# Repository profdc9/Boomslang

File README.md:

# Boomslang

A 3-channel ESP32-S3 pyrotechnic/model-rocket ignition controller. Hardware
(KiCad project, schematic, gerbers) is under `Boomslang/`; firmware is under
`firmware/` (PlatformIO, Arduino framework).

## ⚠️ Disclaimer — use at your own risk

This project fires pyrotechnic devices and/or model rocket motors. Incorrect
wiring, misconfiguration, a firmware bug, a hardware fault, or plain
operator error can cause unintended ignition, fire, injury, or property
damage. **This is a hobbyist project, provided AS-IS, with NO WARRANTY OF
ANY KIND** — express or implied, including no warranty of merchantability,
fitness for a particular purpose, or that it is safe, correct, reliable, or
free of defects.

By building, modifying, or using this hardware or firmware, you accept full
responsibility for:

- Verifying correct operation yourself, on your own hardware, before relying
  on any of it — including every safety feature described in this README.
- Complying with all applicable laws, regulations, and permitting
  requirements for pyrotechnics, explosives, and/or model rocketry in your
  jurisdiction.
- Following standard range-safety practice: safe distances, no bystanders
  in range, appropriate PPE, a real mechanical arm switch you trust, and
  never treating any software feature here as a substitute for that.

The author(s) and contributors accept **no liability** for any injury,
death, damage, or loss arising from building, modifying, or using this
project, to the fullest extent permitted by law.

## License

Dual-licensed by design, since this repo mixes source code and hardware
design files:

- **Firmware** (`firmware/`) is licensed under the [MIT License](LICENSE).
- **Hardware design files** (`Boomslang/` — KiCad schematic, PCB, gerbers)
  are licensed under [CC BY-SA 4.0](LICENSE-HARDWARE.txt).

Both are permissive and allow commercial use, but neither one waives the
disclaimer above — "you can use/modify/redistribute this" is a separate
question from "this is safe or fit for any particular purpose."

## WiFi access

The board hosts its own WiFi AP (no router needed) — SSID and password are
persisted settings (`wifiSsid`/`wifiPassword`, settings page), defaulting to
`boomslang` / `liftoff!`. **The password is this device's only access
control** — there's no separate login on top of it, so anyone who has it can
arm and fire. Change it from the default before using this anywhere it
matters. A password can also be left blank for an open, unencrypted network,
but that isn't recommended for the same reason.

Changes take effect only after the device is power-cycled or reset (the AP
isn't re-initialized at runtime) — you'll need to reconnect using the new
name/password afterward. SSID must be 1-32 characters; password must be
empty or 8-63 characters (the minimum WPA2-PSK allows).

The control pages are served over plain HTTP, not HTTPS — WPA2 already
encrypts the WiFi link itself, and adding TLS on top would mean a
self-signed certificate that a phone would flag as untrusted on every visit,
plus added latency on the page's frequent status polling, for a narrower
additional threat (another authenticated client on the same AP sniffing
traffic) than what WPA2 already covers.

**Relay (station) mode** (`wifiStationMode`, default **off**): instead of
hosting its own AP, the device can join `wifiSsid`/`wifiPassword` as a
client of an existing router, to relay through it when the operator needs
more distance from the pyrotechnics than the device's own AP range allows.
If it can't connect within 15 seconds (wrong password, out of range, router
down), it falls back to hosting its own AP instead — so a bad relay network
never leaves you locked out of the device with no way to disarm or abort.

This setting is deliberately **not a checkbox** on the settings page:
enabling it means anyone who can reach that external network can also reach
this device, so it requires typing the literal word `relay` into a text
box rather than a single accidental tap — blank or anything else both mean
"stay off, host my own AP" (the safe default), including if the field is
missing from the request entirely.

**Before you enable this, secure that router/network yourself — it's now
part of your access control, not just Boomslang's own password.** In its
own AP mode, WPA2 on the device is the entire perimeter. In relay mode,
that perimeter is whatever the router enforces: WPA2/WPA3 with a strong
password of its own, no other untrusted devices or guests on it, and
ideally a network used for nothing but this. A relay network that's open,
weakly secured, or shared with devices you don't control gives *anyone on
it* the same access as someone standing next to the device with its own
password — arming and firing included.

Either way — hosting an AP or joined as a station — the device also starts
an mDNS responder, so `http://boomslang.local` works regardless of which
mode ended up active or what IP a router's DHCP server happened to assign.

## Web UI pages

Four pages, all polling `/status.json` and posting to the same handful of
endpoints — the split below is purely how the browser organizes things, not
a backend/data-model split. Each has a small nav row (Main · Timing · Stats
· Settings) so it's obvious how to get back to the others.

- **`/` (Main)** — the operational screen, meant for actual field use:
  arm/fault/lockout status, battery voltage, each channel's checkbox + live
  continuity/firing state, and TRIGGER/ABORT/PANIC. Deliberately lean —
  timing setup and post-fire review live elsewhere so this screen stays fast
  to read and tap through during an actual arm/fire sequence.
- **`/timing`** — setup screen: the same channel checkboxes as Main (same
  `/select` endpoint — selection can be changed from either page) plus each
  channel's offset/duration in milliseconds and optional PWM cycling
  (Hz/duty%, see Trigger sequence below). No live operational state and no
  TRIGGER/ABORT/PANIC here.
- **`/stats`** — read-only review: peak and average current per channel
  from its most recent pulse (see Trigger sequence below).
- **`/config` (Settings)** — every persisted setting described throughout
  this README.

## Overcurrent fault protection

Each channel's IRLZ44N MOSFET has its own analog overcurrent comparator
(transistors Q5/Q10/Q16, sensing the 0.05Ω source shunt) that pulls that
channel's own gate to GND in hardware, in nanoseconds, with **no firmware
involved at all**. That's the actual protection for the transistor. All
three channels' comparators also pull a single shared, open-collector,
active-LOW `FAULT` line (GPIO1) — since it's wired-OR across all three,
firmware can tell *that* a channel faulted, but not *which* one.

The 0.05Ω figure above is just the schematic default (R1/R17/R31) — the
per-channel shunt resistance (`senseOhms`, settings page) is a runtime
setting used for the firing-current math (`readCurrentA()`), independently
of the comparator's own fixed hardware trip point. Valid range is
**0.01Ω–100Ω**, to accommodate a field-replaced shunt of a different value.

**The fault ISR** (`onFaultISR` in `firmware/src/main.cpp`) is a level-1
`attachInterrupt` on `FAULT`, `IRAM_ATTR`, and deliberately minimal: it does
exactly two things, a single register write forcing all three TRIGGER
outputs HIGH at once (not just the channel that faulted — the shared line
can't tell which one anyway, so every channel is shut down for consistency)
and setting a sticky `faultLatched` flag. Nothing else runs in the ISR
itself — no `Serial`, no heap, and critically no `analogRead()`, since the
ESP-IDF ADC driver takes a FreeRTOS mutex internally that `loop()` is
already holding on a regular basis; taking it again from ISR context would
be undefined behavior.

**Sampling SENSE for diagnostics** (which channel was drawing how much
current right as the fault hit) therefore happens in a separate,
dedicated FreeRTOS task (`faultSampleTask`), woken by the ISR via
`vTaskNotifyGiveFromISR`/`portYIELD_FROM_ISR` so it runs essentially the
instant the ISR returns, ahead of `loop()` or anything else. It's pinned to
the core opposite the Arduino loop/web server, at a priority high enough to
preempt normal code but below WiFi's own internal tasks. This snapshot is
best-effort — the hardware protection may have already cut current before
it runs — and is exposed as `fault_snapshot_a` in `/status.json` and shown
in the FAULT banner on the control page. If the banner reads "FAULT —
overcurrent detected" with no `(X.XXA Y.YYA Z.ZZA)` after it, that means
`fault_snapshot_a` was never populated for this event — either
`writeTriggerPinBlanked()`'s own fallback latched the fault directly
(covered below; it takes its own snapshot too, since it's normal task
context rather than ISR context and can safely call `analogRead()`
itself, unlike `onFaultISR()`), or a fault was latched some other way that
doesn't notify `faultSampleTask` (the boot-time check, for example).

**Clearing a fault**: `faultLatched` is a software latch, not
self-clearing. It clears automatically — no button, no endpoint — the
instant the device is `DISARMED` and the hardware `FAULT` line re-checks
clear (several reads over ~2ms, so a line chattering right at the trip
point doesn't get cleared into a still-live fault; see `loop()`'s
DISARMED-only fault-clearing pass in `main.cpp`). It's tied specifically
to being disarmed — never while armed, so a fault mid-sequence can't clear
itself out from under an operator who hasn't actually disarmed — which
matches the fact that a disarm+rearm is already required before
retriggering anyway (see `faultLockedOut()` below); there was no reason to
also require a separate manual "clear fault" button on top of that. A
reboot doesn't clear a persistent fault either: `FAULT` is checked at
boot, before the ISR is even attached, and latches immediately if still
asserted.

**Fault lockout** (`faultLockedOut()`/`notifyFaultOccurred()`,
`arm_state.cpp`): independent of `faultLatched` above — that flag only
tracks whether a fault is *currently* asserted/unacknowledged, and clears
automatically as soon as it's genuinely resolved and the device is
disarmed. This is a separate, sticky flag: once any fault has occurred, it
stays set — same shape as the PANIC lockout — unconditionally requiring a
fresh disarm+rearm before another TRIGGER is accepted, regardless of
`requireRearmAfterFire`, even after the fault itself has already cleared.
Cleared at the same disarm→rearm transition point every other lockout is.

**Live FAULT line indicator**: the main control page also shows a
`FAULT line: clear/ASSERTED` readout (`fault_pin_active` in
`/status.json`, a plain `digitalRead(PIN_FAULT)` taken fresh on every
poll), separate from the latched `fault` flag above. Since `faultLatched`
only clears automatically while disarmed, this raw reading is what tells
you whether the hardware comparators are asserting the line *right now* —
useful for telling "latched from a past event, line's gone high again"
apart from "still actively faulted."

**Leading-edge blanking on trigger-pin switching**: on real hardware,
pressing TRIGGER with no igniter/load connected was found to produce an
immediate `FAULT` with a 0A current snapshot — a switching transient at the
moment a trigger pin changes state, not a real overcurrent event (confirmed
by walking the actual shunt/comparator/snubber netlist: the RC snubber ties
drain-to-GND directly, not through the sense shunt, so there's no real
current path for a genuine fault with nothing connected). `firmware/src/
main.cpp`'s `writeTriggerPinBlanked()` now wraps the two deliberate
trigger-pin writes (fire-start in `startFirePulse()`, and the normal
pulse-end release in `loop()`) in a short critical section
(`FAULT_BLANKING_US`, `config.h`, default 10µs — tuned down from an
initial 30µs guess after bench testing confirmed the real switching
transient clears well within that window): interrupts are disabled
for that window, the pin is written, and `FAULT` is checked once directly
afterward — if it's already resolved, that reading is trusted and the
event is treated as filtered, not a fault.

Two subtleties this required getting right, since a plain
`delayMicroseconds()`-based wait would not have been safe here:

- `noInterrupts()`/`interrupts()` (not `detachInterrupt()`/
  `attachInterrupt()` + a bare delay) bounds the window deterministically —
  a plain busy-wait doesn't block task preemption, so a higher-priority
  task/ISR becoming ready mid-wait could otherwise extend the real gap well
  past `FAULT_BLANKING_US`. `delayMicroseconds()` itself is safe to call
  with interrupts disabled: it polls `micros()`, which reads a free-running
  hardware counter that keeps advancing regardless of the core's
  interrupt-enable state — unlike `delay()`/`vTaskDelay()`, which actually
  depend on the tick interrupt to wake back up, and would hang here.
- Disabling interrupts at the CPU level only defers *servicing* — it
  doesn't stop the GPIO peripheral's own edge-detector from latching a
  FALLING edge into its interrupt-status register during the window. Left
  alone, a transient that resolves *inside* the window would still fire
  `onFaultISR()` retroactively the instant interrupts are re-enabled, for
  an edge that's already history. `writeTriggerPinBlanked()` explicitly
  clears that latched status bit (`GPIO_STATUS_W1TC_REG`) before
  re-enabling, so a resolved transient is actually discarded.

None of this touches the real transistor protection described above — the
per-channel analog comparators keep working purely in hardware throughout,
completely independent of whether this interrupt is masked. What's
filtered is only the shared-line firmware echo (forced shutoff + the
sticky latch) reacting to a switching artifact instead of a real fault.

**Why `FAULT_BLANKING_US` isn't 0**: it's tempting to think a shorter
window is strictly better (less time other channels go unprotected by the
shared-line echo — the per-channel hardware protection is never affected
either way). Bench testing found a real lower bound, though: at `0`
(no wait at all), a genuine fault could be missed by `writeTriggerPinBlanked()`
entirely rather than filtered — the comparator's own output hadn't
necessarily finished settling into a stable level by the instant this
function checks it, so a real, ongoing fault could read as
"already resolved" and get discarded, only to be caught later by some
other, slower path with no diagnostic snapshot at all. `10µs` reliably
avoids that while still filtering the original no-load transient. The
delay also determines *where* on the fault current's natural rise/decay
curve the diagnostic snapshot below lands: shorter delay samples closer to
the true peak, longer delay samples further into the decay (current
doesn't collapse to zero the instant the comparator trips — the driver
stage and any loop inductance both take some real, if small, additional
time). `10µs` was chosen empirically on the bench, not derived
analytically — if the real transient/settling duration ever needs to be
known precisely, `DEBUG_FAULT_TIMING`/GPIO13 above is there for exactly
that.

**`writeTriggerPinBlanked()`'s fallback and multi-channel shutoff**: if
`FAULT` is still asserted once the blanking window elapses, this function
also samples SENSE for its own diagnostic snapshot (same reasoning as
`faultSampleTask` above — normal task context, so `analogRead()` is safe
here too) and forces every trigger pin off via the same atomic register
write `onFaultISR()` uses, mirroring what the ISR does for a fault that
isn't coincident with a trigger-pin write. This closes a real gap found
during testing: with a real load on one channel and a short on another,
if the short's fault was caught by this fallback (i.e. it happened right
at that *other* channel's own trigger-pin write) rather than by
`onFaultISR()`, the loaded channel could keep firing for longer than
intended — this function used to only set the sticky fault flags and rely
on `loop()`'s later `stopSequence()` call to shut off *other* channels,
reached only after that iteration's other work (continuity checks, etc.).
Forcing every pin off directly here, immediately, closes that gap the
same way the ISR always has.

The sampling happens *before* that forced shutoff, deliberately: forcing
every channel off first, before sampling, was found to reliably collapse
the diagnostic reading to 0A — unlike the local hardware protection, which
reacts in true analog time and was never the bottleneck here,
`analogRead()` itself is not deterministic (the underlying ESP-IDF driver
power-cycles the whole ADC peripheral and takes an internal mutex on every
single call), so forcing a shutoff immediately beforehand left nothing
meaningful to measure by the time sampling actually ran. Sampling first
trades a small amount of additional, ADC-read-bound latency before *other*
channels are forced off, for a snapshot that's actually usable — still
bounded well under the IRLZ44N's ~1ms SOA tolerance, just no longer
effectively instantaneous the way the plain register write is on its own.

Why a plain level-1 interrupt is enough: the IRLZ44N's SOA tolerates ~1ms at
full overcurrent, and even level-1 ISR latency on this chip is reliably
single-digit microseconds — comfortably inside that margin, especially
given the hardware analog protection has already started cutting current
before the ISR even runs. A `DEBUG_FAULT_TIMING` build flag (on by default
in `config.h`) toggles a spare pin (GPIO13) around ISR entry and the end of
SENSE sampling, so real end-to-end latency can be measured on a scope once
hardware exists.

**`DEBUG_DISABLE_FAULT_SHUTOFF`** (`config.h`, default **off**): a
bench-debug-only build flag used while diagnosing the switching transient
above. When on, it skips firmware's forced-HIGH/`stopSequence()` echo on a
fault, letting an in-progress pulse keep running through a `FAULT` trip
instead of being cut short — useful for observing what's actually
happening with no load connected. `faultLatched` is still set and still
blocks new triggers until disarmed and genuinely resolved, same as
always; only the forced shutoff of an already-running pulse is skipped.
It does **not** and cannot
affect the real per-channel hardware protection described above, which
runs in pure analog and has no firmware involvement at all. Must be off
for any real use with igniters/pyrotechnics connected.

## Audible / visible arming indicators

The board carries a buzzer output (`J6`, driven via `AUDIBLE`/GPIO41) and
onboard white/blue strobe LEDs (driven via `VISIBLE`/GPIO42). Both are owned
entirely by the firmware's arm state machine (`firmware/src/arm_state.cpp`)
— there's no manual on/off control for them, since a manual override would
just fight the automatic pattern.

**When they run:** only while the arm loop (the physical switch at `J5`) is
closed — i.e. during the `COUNTDOWN` and `READY` states. They're silent and
dark whenever the device is `DISARMED`; there's nothing to warn about when
the loop is open.

**Why two different patterns:** so the state can be told apart by ear or by
eye alone, without needing to look at the web UI:

| State       | Tone    | Pulse rate           |
|-------------|---------|-----------------------|
| `COUNTDOWN` | 440 Hz  | ~1 Hz (slow, 500ms on/off) |
| `READY`     | 1000 Hz | ~2.5 Hz (fast, 200ms on/off) |

A low, slow pulse means the countdown is still running and firing is *not*
yet permitted (giving whoever closed the arm switch time to clear the area).
A higher, faster pulse means the countdown has elapsed and the device is
ready to fire.

**Tone stability:** `updateArmState()` runs every `loop()` iteration
(unthrottled, so potentially thousands of times per second), but only
touches the buzzer's LEDC output on an actual change — turning on, turning
off, the frequency changing, or the volume changing — rather than every
iteration. Arduino's `tone()`/`noTone()` aren't used here: `tone()`
reprograms the ESP32's LEDC PWM peripheral and resets phase on every call
(producing an audible click if called continuously — the original cause of
a choppy/glitchy buzzer sound), and it always drives a fixed 50% duty
cycle, which rules it out for volume control (below) regardless. Frequency
and duty are set independently instead, via `ledcChangeFrequency()`/
`ledcWrite()` (`AUDIBLE_LEDC_CHANNEL`, `config.h`).

**Volume:** `speakerVolume` (settings page, 0-10, default **10**) maps
linearly to 0-50% PWM duty cycle — 50% is as loud as a square-wave drive
gets (maximum RMS), so 10 reproduces the same loudness `tone()` always
used before this was configurable. Recomputed every `updateArmState()`
call, so changing it takes effect immediately, live, with no disarm/rearm
needed.

**Settings:** each channel can be silenced independently via the settings
page (`/config` on the web UI):

- `visibleWhenArmed` — strobe LEDs flash during `COUNTDOWN`/`READY` (default **on**)
- `audibleWhenArmed` — buzzer sounds during `COUNTDOWN`/`READY` (default **on**)
- `speakerVolume` — buzzer loudness, 0-10 (default **10**, see above)

All are persisted to flash (survive power cycles) and, like all settings
changes, can only be saved while the device is disarmed.

## Trigger sequence

Firing isn't one button per channel — the main control page lets you select
which channels to fire and, per channel, how long after pressing TRIGGER
that channel should fire, then fires the whole configured sequence off a
single press.

**Per channel:**
- A checkbox, on both the Main and Timing pages, to include that channel in
  the next trigger. **Not** persisted — it resets on every page load, so a
  stale "everything selected" state from a previous session can never carry
  over silently. It also resets on every device *reboot*, which the page
  detects on its own: `/status.json`'s `uptime_ms` resets to a small value
  on every boot, and if a poll ever sees it drop compared to the previous
  poll, that means the device restarted since then — the page then rebuilds
  its channel list from scratch on the next poll, so a browser tab left
  open across a power cycle can't keep showing checked boxes that no longer
  match the device's actual (cleared) selection.
- An **offset** in milliseconds (0-60000, default 0), on the Timing page,
  from the TRIGGER press to that channel's trigger output going low.
- A **duration** in milliseconds (0-30000, default 500), also on the Timing
  page, that the trigger output then stays low.

Offset and duration are both persisted settings
(`channelDelayMs`/`channelDurationMs`), saved to flash the moment you change
either one — same as every other setting, they survive a power cycle, so a
fixed show sequence doesn't need retyping every session. They're plain
milliseconds rather than seconds specifically for finer-grained control over
short pulses. Also same as every other setting: saving to flash requires
the device to be disarmed — a change made while armed still applies
immediately in RAM for that session, but won't survive a reboot until you
disarm and it actually gets persisted.

**PWM cycling** (`channelPwmHz`/`channelPwmDutyPercent`, Timing page, per
channel): instead of being continuously on for the whole duration, a
channel can instead cycle on/off within that same duration window — for a
lower average heating rate than a full-on pulse (e.g. slow-heating
nichrome/resistive element rather than an instant e-match). `channelPwmHz`
(0-300Hz, default **10Hz**, `0` disables PWM — continuously on for the
whole duration, exactly as before) sets the cycle rate; `channelPwmDutyPercent`
(0-100%, default **100%**) sets how much of each cycle is on. 100% duty
(the default) is treated the same as PWM being disabled — continuously on,
no cycling — so a fresh board fires exactly as it always did until duty is
deliberately lowered; 0% duty delivers no power at all for the whole
duration. This is a plain software timer in `loop()`, not hardware PWM.

**300Hz is a real, bench-measured ceiling, not just "doesn't need to be
precise."** The toggle logic can't act faster than `loop()` itself
iterates: at a PWM period comparable to one `loop()` iteration, both the
on-phase and off-phase end up bottlenecked by the same iteration time
instead of the requested durations, and duty accuracy collapses — 1000Hz
was measured converging toward ~50% regardless of configured duty,
regardless of how fast `loop()` was made to run. `loop()`'s own rate was
itself a real bottleneck worth fixing along the way: `WebServer::
handleClient()` calls a flat `delay(1)` whenever no HTTP client is
actively mid-request (i.e. most of the time), which is `vTaskDelay()`-
backed and rounds up to at least one full FreeRTOS tick (1ms, this
project's `CONFIG_FREERTOS_HZ=1000`) — capping `loop()` at ~1kHz
regardless of how much other per-iteration work was reduced. `main.cpp`'s
`setup()` now calls `server.enableDelay(false)` to remove that floor,
which alone raised the measured rate from ~1kHz to ~3kHz. At that rate,
300Hz (30 iterations/period) keeps duty tracking usable down to about 10%
duty; a `DEBUG_LOOP_RATE` build flag (`config.h`, on by default) logs the
actual measured rate over Serial once a second if this ever needs
re-checking on different hardware.

**Every PWM edge gets the same protection as a single trigger-on event**:
each on/off transition, not just the first, goes through
`writeTriggerPinBlanked()` (see Overcurrent fault protection above), so a
fault at any point during a PWM burst is caught exactly the same way it
would be for a plain single-shot fire. Turning *off* is always immediate;
before turning back *on* at each cycle, firmware re-checks fault/armed/
continuity — the same belt-and-suspenders re-check described below for the
initial fire-time check, just repeated at every cycle rather than once,
since a PWM burst can run for a while. A failed re-check stops that
channel's remaining cycles for the rest of the sequence rather than
retrying.

**Pressing TRIGGER** is only possible when `arm_state` is `READY`, there's no
active fault, no sequence is already running, and (if
`requireRearmAfterFire` is on) the device hasn't fired since it was last
armed. It schedules every selected channel's trigger output to go low at
`now + its configured offset`, for its configured duration, then
immediately blocks further TRIGGER presses until that sequence finishes
(you can never have two sequences in flight at once, regardless of
settings).

**At each channel's actual fire moment** — not just when TRIGGER was pressed
— the firmware re-checks armed state, fault, and continuity. An offset can
be long enough for something to change, so a channel that fails this
recheck is skipped (and logged) rather than aborting the rest of the
sequence. If the arm switch is opened mid-sequence, the gate drivers lose
power outright regardless of what firmware does — this recheck is
belt-and-suspenders, not the actual safety mechanism.

**`requireRearmAfterFire`** (settings page, default **on**): once a trigger
sequence has run, no further TRIGGER is accepted until the arm switch is
opened and closed again (a fresh disarm + countdown + `READY`). With it off,
another TRIGGER is accepted as soon as the current sequence finishes, no
rearm needed.

**Peak and average current**, per channel, for its most recent pulse: while
a channel's trigger output is low, `firmware/src/main.cpp`'s `loop()`
samples that channel's current sense on every iteration, tracking the
highest single sample (peak) and the running mean of all samples (average).
Both are reset at the start of each pulse and then simply held afterward —
so they remain readable (`peak_current_a`/`avg_current_a` in
`/status.json`, shown per channel on the `/stats` page) for the rest of the
session, until that channel fires again. Sampling continues every
iteration regardless of PWM on/off phase, so the average comes out
duty-cycle-weighted automatically — off-phase samples read ~0A and pull it
down proportionally — with no special-case math needed. The main control
page's live "FIRING" status shows this running average rather than the
instantaneous reading while a channel is actively firing, since the
instantaneous value is sampled at an arbitrary instant relative to the PWM
cycle (the page polls every 500ms) and would otherwise often show ~0A
simply by catching an off-phase, even with real current flowing during
on-phases.

## ABORT and PANIC buttons

Two more buttons sit below TRIGGER on the main control page, both backed by
a shared `stopSequence()` helper (`firmware/src/main.cpp`) that stops
things *immediately* — any channel mid-pulse has its trigger pin forced
back HIGH right away rather than waiting out the rest of the fire pulse,
and anything still scheduled (waiting on its configured delay) is
cancelled. Neither has a confirm dialog on the frontend, and neither is
gated on any precondition — an abort/panic button should always just work,
the instant it's tapped, like a real E-stop.

**ABORT** (`/abort`) just stops the sequence. It does **not** prevent
retriggering — if the device is still armed and ready afterward, TRIGGER is
available again immediately. Only enabled on the control page while a
sequence is actually running, since it has nothing to do otherwise.

**PANIC** (`/panic`) does the same immediate stop, and *additionally*
always sets a new lockout (`panicLockedOut()` in `arm_state`) requiring a
full disarm and rearm before another TRIGGER is accepted — unconditionally,
independent of `requireRearmAfterFire`, and regardless of whether anything
was actually firing when it was pressed. Always enabled on the control
page, since pressing it has an effect either way.

## Arm timeout (auto-lockout)

Guards against "armed and walked away": if the device sits in `READY` —
armed, past the countdown, but never actually triggered — for longer than a
configurable timeout, TRIGGER is refused until a fresh disarm and rearm,
even though the arm switch (`J5`) is still physically closed.

**`armTimeoutSec`** (settings page, default **600s / 10 minutes**, 0
disables it): the clock starts the instant `COUNTDOWN` transitions to
`READY`, not when the switch was first closed, so a long
`armCountdownSec` doesn't eat into the READY window. Once it elapses, the
control page shows "Arm timeout elapsed — disarm & rearm required before
triggering again" and TRIGGER is disabled, the same way it is for
`panicLockedOut()` — cleared at the same point every other lockout is: the
arm switch observed open, then closed again.

This is a **software-only** lockout, same family as PANIC and the
continuity/rearm lockouts above: it cannot re-power the gate drivers on its
own, and it cannot cut them either. It only blocks the firmware's own
`/trigger` handler. The hardware arm switch remains the actual power
interlock regardless of this setting — the buzzer/strobe pattern keeps
following `READY` normally throughout, since electrically the device really
is still armed.

## Continuity checks

`CONTINUITY1/2/3` sense the same way `SENSEFAILSAFE` does: ~1mA through a red
LED, whose forward voltage exceeds `LED_CLAMP_ARM_VOLTS` (1.25V,
`firmware/src/config.h`) when the loop (the igniter, in this case) is
actually closed. That threshold (`CONTINUITY_OK_RAW` in the same file) is
shared with the arm-loop sense, since it's the identical circuit at the
identical target voltage.

Beyond the per-channel status dot, continuity gates channel selection and
triggering in two independent ways:

**Arm-time continuity monitor** (`checkContinuityOnArm`, settings page,
default **on**): while armed (`COUNTDOWN` or `READY`), continuously verifies
that every *selected* channel still has continuity. If one doesn't, the
control page shows an error and TRIGGER is refused — but this is live, not
latched: it clears itself the instant continuity is restored, or the setting
is turned off, no disarm needed. While this setting is on, channel selection
is also locked while armed (the `/select` endpoint refuses changes), since
the set of channels being monitored can't shift out from under a live check
— disarm to change which channels are selected.

This monitor reads `channelContinuityCached` rather than sampling fresh
every `loop()` iteration — `main.cpp`'s `loop()` round-robins one
`analogRead()` per iteration across battery voltage and each channel's
continuity (`slowSampleStep`, cycling through `NUM_CHANNELS + 1` steps)
instead of sampling all four every time, so each value is at most a few
iterations stale (comfortably fast relative to what actually reacts to
them — this monitor is already explicitly best-effort/self-clearing, and
the low-voltage lockout below already debounces over 2 seconds). This was
one of several fixes to a real, measured bottleneck: each `analogRead()`
call was found to carry real, non-trivial overhead (the underlying
ESP-IDF driver power-cycles the whole ADC peripheral and takes an internal
lock on every call), and `loop()` was doing up to 9 of them per iteration
in the fully-armed-and-monitoring case. The pre-trigger check and the
per-channel fire-time recheck below both still call `hasContinuity()`
directly for a fresh, uncached read — this round-robin cache is only used
for the informational background monitor, never for a safety-relevant
check made right before actually energizing a channel.

**Pre-trigger continuity check** (`checkContinuityBeforeTrigger`, settings
page, default **on**): at the instant TRIGGER is pressed, re-verifies
continuity for every selected channel. If any fail, *nothing* fires, the
control page shows an error, and — unlike the live monitor above — this is a
hard lockout: a full disarm and rearm is required before another TRIGGER is
accepted, regardless of `requireRearmAfterFire` (that setting is about the
post-*successful*-fire case; this is a separate, always-strict rule for this
specific failure).

Both checks are additional to, not a replacement for, the per-channel
recheck already described under Trigger sequence above (which happens at
each channel's actual fire moment, not at the TRIGGER press, and only skips
that one channel rather than refusing the whole sequence).

## Battery voltage

The 12V supply is sensed on GPIO2 through a fixed 1:11 resistor divider
(`BATTERY_DIVIDER_RATIO` in `firmware/src/config.h` — a PCB-fixed ratio, not
a runtime setting like the current-sense shunts), after passing through a
series diode ahead of the divider. `readBatteryVoltage()` (`main.cpp`) adds
back that diode's forward drop (`BATTERY_DIODE_DROP_V`, 0.7V, also a
compile-time constant — it's a fixed part characteristic, not field-
adjustable) so `battery_v` reflects true battery voltage, not the
diode-reduced rail. The reading is shown on the main control page as
`battery_v`.

The low-voltage lockout decision (below) uses this exact same reading —
`updateArmState()` takes `battery_v` as a parameter rather than sampling
`PIN_BATTERY` a second time independently, which it originally did. The
two readings need to agree: they briefly didn't (a since-fixed bug), and
the lockout could compare an uncorrected value against the threshold while
the banner showed the corrected `battery_v`, so the displayed voltage in a
"Cannot arm — battery too low" message could be well above the threshold
it had supposedly tripped. Sharing one reading both fixes that class of
bug structurally (there's only one value to ever disagree with itself) and
avoids a redundant `analogRead()` every `loop()` iteration — see the
round-robin sampling note under Continuity checks below, which this same
mechanism also covers.

**Low-battery warning:** below `lowBatteryThresholdV` (settings page,
default **11.5V**), the battery readout on the control page turns orange and
bold and appends "LOW BATTERY". This is just a warning — on its own it
doesn't stop you from arming or triggering.

**Low-voltage lockout** (`lowVoltageLockoutEnabled`, default **on**): reuses
the same threshold to actually block operation, independent of the warning
display:

- If the arm switch closes while `battery_v` is under threshold, the device
  stays `DISARMED` instead of entering `COUNTDOWN`.
- If voltage drops below threshold *while already* in `COUNTDOWN` or
  `READY`, the device is forced back to `DISARMED` immediately — the same
  path as the arm switch opening, including aborting any in-flight trigger
  sequence.

Both cases are live, not latched: checked continuously, not just at the
moment the switch closes. If the switch is still closed when voltage drops
too low, the control page shows "Cannot arm — battery too low"; the instant
voltage recovers above threshold, arming proceeds normally on its own,
with no need to open and reclose the switch. Turn the lockout off in
settings to arm anyway regardless of voltage (e.g. bench testing on a
supply that's intentionally below threshold) while keeping the warning
display active.

**Debounce and hysteresis** on the voltage check itself (`arm_state.cpp`),
addressing two failure modes a single raw comparison would otherwise have:

- *Boundary flapping* — a reading oscillating right at the threshold (ADC
  noise, supply ripple) could otherwise flap the lockout in and out rather
  than settling. Once locked out, voltage must recover past
  `lowBatteryThresholdV + 0.3V` (not just past the threshold itself) before
  the lockout clears.
- *Self-induced false trip* — firing an igniter draws real current through
  the same 12V rail being sensed, so a fire pulse can sag `battery_v`
  momentarily. The low-voltage condition must hold steady for 2 seconds
  (comfortably longer than a typical `channelDurationMs` pulse, or a short
  multi-channel burst) before the lockout actually engages, so a firing
  event's own transient sag isn't mistaken for a real low battery.

This is the same debounce shape `SENSEFAILSAFE` already uses for the arm
switch itself, just with a longer window and added hysteresis suited to a
noisier, slower-moving analog signal rather than a mechanical switch.

## Factory reset

`PIN_FACTORY_RESET` (GPIO14) is pulled up internally and checked once,
early in `setup()`, before settings are loaded. Ground it — a jumper or
button to GND — before powering the board up, and every setting resets to
its compiled-in default and is immediately persisted to flash, overwriting
whatever was there. It's checked with a few reads over a couple of
milliseconds rather than a single instantaneous one, so a pin still
settling right after `pinMode()` doesn't trigger a reset by accident.

This only runs at boot, from a floating/undriven starting point — there's
no runtime "hold this pin for 10 seconds" monitor. GPIO14 has no strapping
or other special function on the ESP32-S3 (unlike GPIO12 on the *original*
ESP32, a common source of outdated advice online — that specific gotcha
doesn't carry over to the S3), and is otherwise unconnected on the PCB.

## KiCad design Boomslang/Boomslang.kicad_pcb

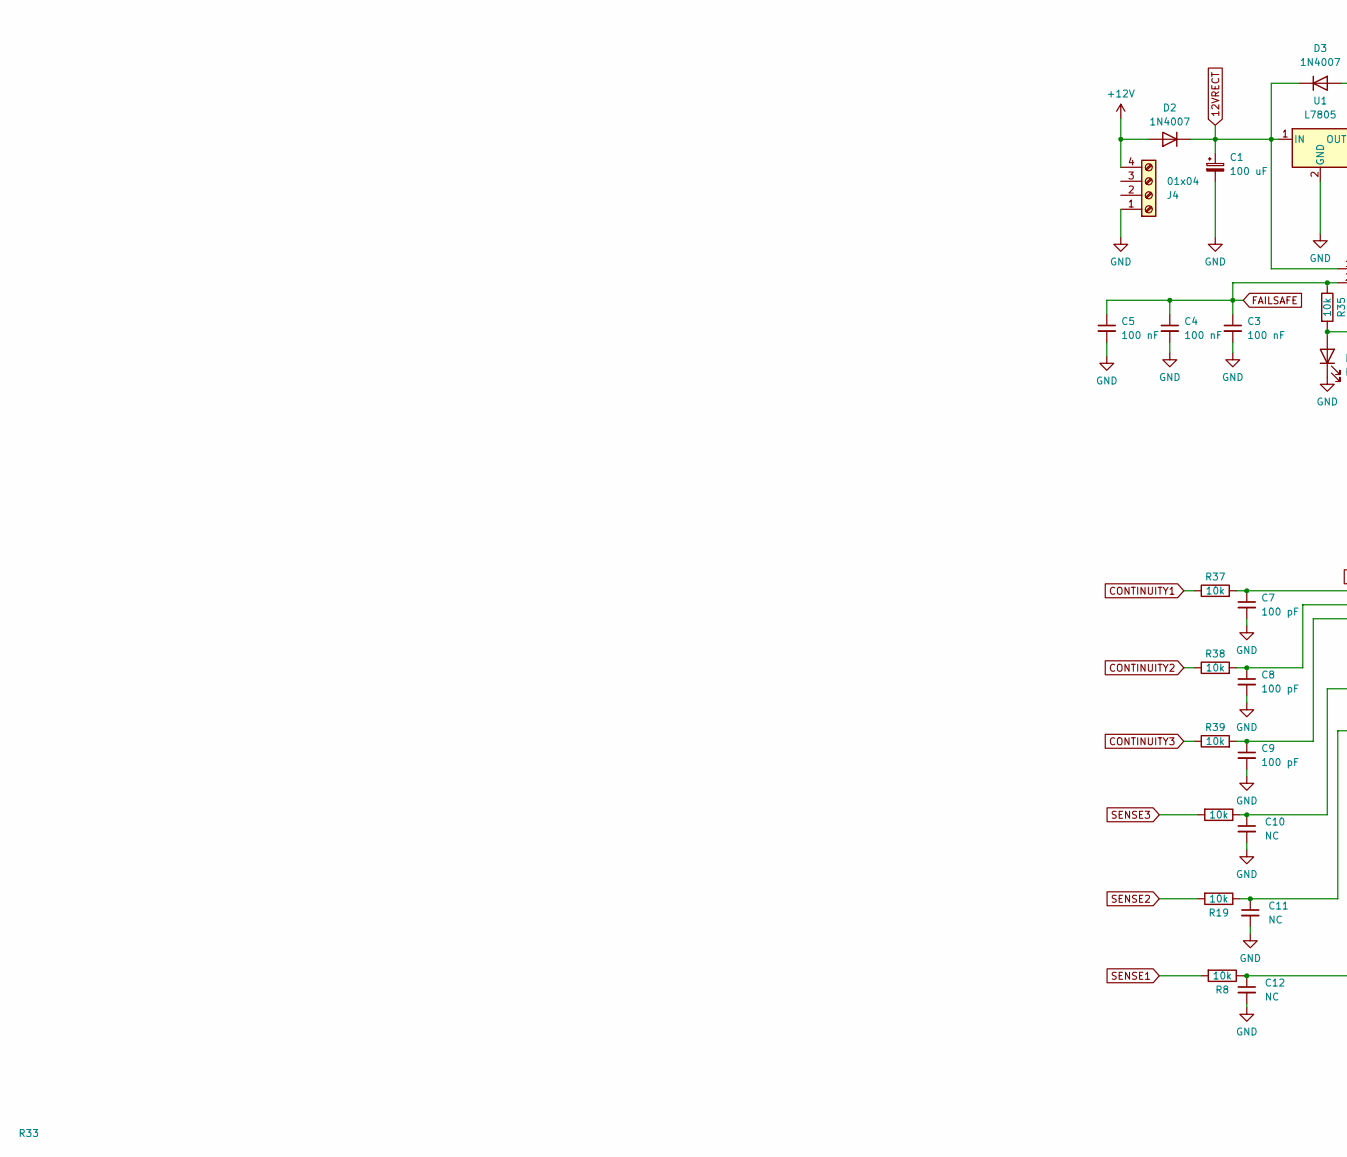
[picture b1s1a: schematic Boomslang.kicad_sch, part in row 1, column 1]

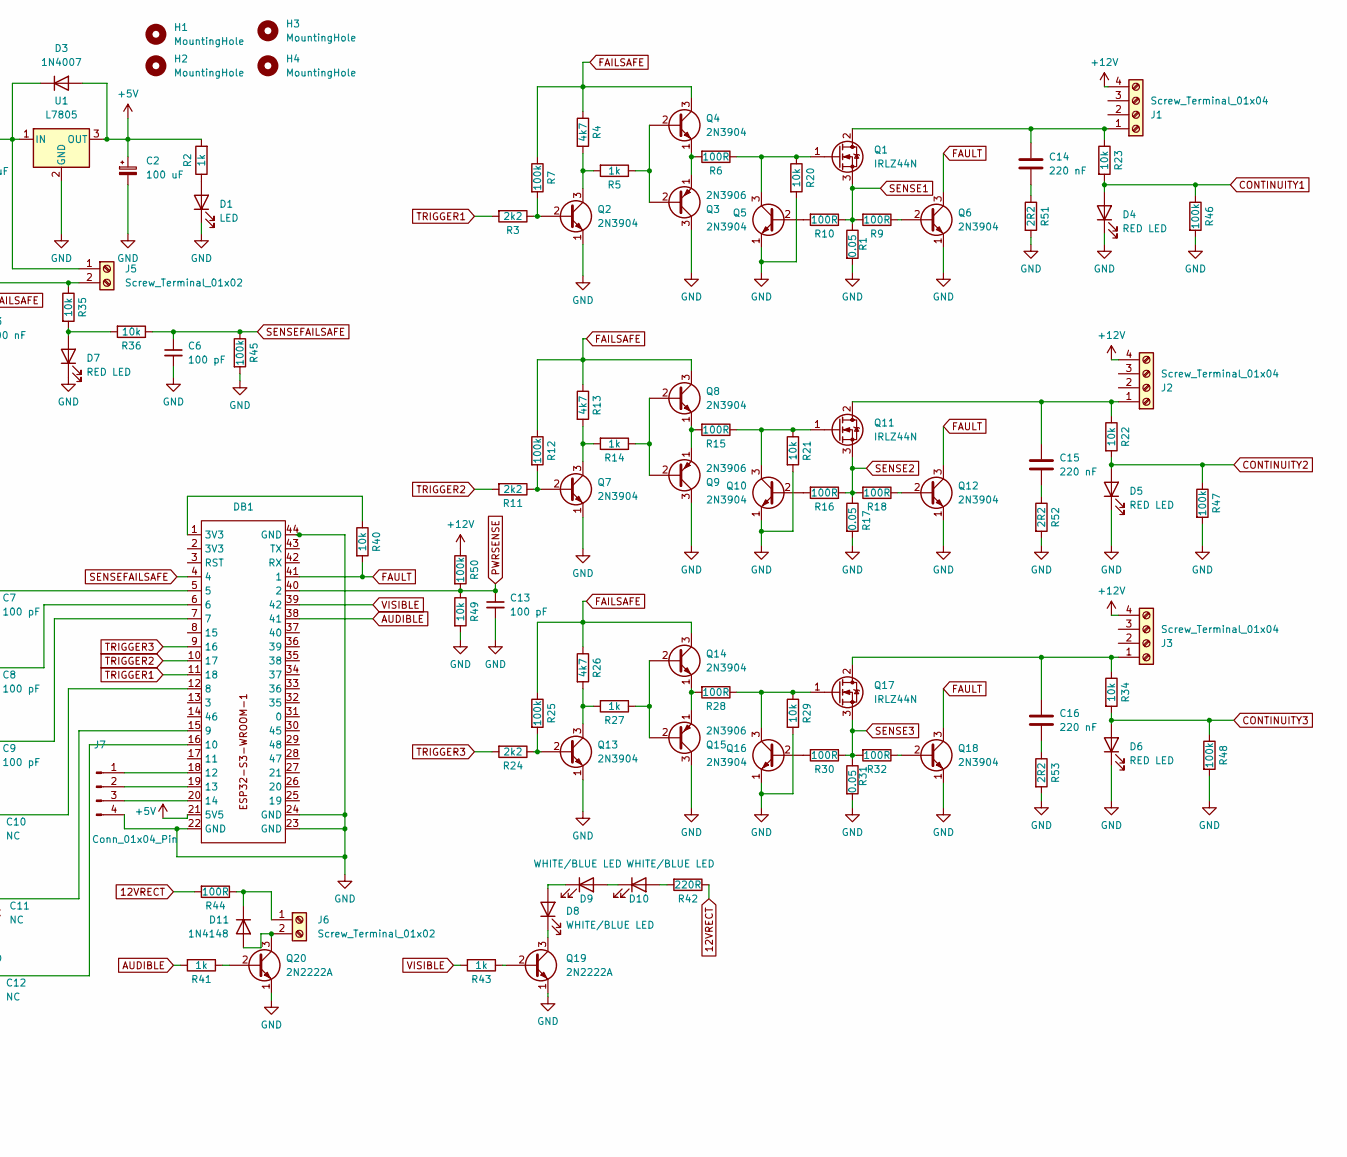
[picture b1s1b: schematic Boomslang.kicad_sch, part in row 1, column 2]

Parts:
C1, C2: 100 uF; CP_Radial_D7.5mm_P2.50mm
C3, C4, C5: 100 nF; C_Disc_D5.0mm_W2.5mm_P5.00mm
C6, C7, C8, C9, C13: 100 pF; C_Disc_D5.0mm_W2.5mm_P5.00mm
C10, C11, C12: NC; C_Disc_D5.0mm_W2.5mm_P5.00mm
C14, C15, C16: 220 nF; C_Rect_L7.0mm_W2.5mm_P5.00mm
D1: LED; LED_D5.0mm
D2, D3: 1N4007; D_DO-41_SOD81_P7.62mm_Horizontal
D4, D5, D6, D7: RED LED; LED_D5.0mm
D8, D9, D10: WHITE/BLUE LED; LED_D5.0mm
D11: 1N4148; D_DO-41_SOD81_P7.62mm_Horizontal
DB1: ESP32-S3
H1, H2, H3, H4: MountingHole; MountingHole_3.2mm_M3
J1, J2, J3: Screw_Terminal_01x04; TerminalBlock_bornier-4_P5.08mm
J4: 01x04; TerminalBlock_bornier-4_P5.08mm
J5, J6: Screw_Terminal_01x02; TerminalBlock_bornier-2_P5.08mm
J7: Conn_01x04_Pin; PinSocket_1x04_P2.54mm_Vertical
Q1, Q11, Q17: IRLZ44N; TO-220-3_Vertical
Q2, Q4, Q5, Q6, Q7, Q8, Q10, Q12, Q13, Q14, Q16, Q18: 2N3904; TO-92_Inline_Wide
Q3, Q9, Q15: 2N3906; TO-92_Inline_Wide
Q19, Q20: 2N2222A; TO-92_Inline_Wide
R1, R17, R31: 0.05; R_Axial_DIN0414_L11.9mm_D4.5mm_P15.24mm_Horizontal
R2, R5, R14, R27, R41, R43: 1k; R_Axial_DIN0207_L6.3mm_D2.5mm_P7.62mm_Horizontal
R3, R11, R24: 2k2; R_Axial_DIN0207_L6.3mm_D2.5mm_P7.62mm_Horizontal
R4, R13, R26: 4k7; R_Axial_DIN0207_L6.3mm_D2.5mm_P7.62mm_Horizontal
R6, R9, R10, R15, R16, R18, R28, R30, R32: 100R; R_Axial_DIN0207_L6.3mm_D2.5mm_P7.62mm_Horizontal
R7, R12, R25, R45, R46, R47, R48, R50: 100k; R_Axial_DIN0207_L6.3mm_D2.5mm_P7.62mm_Horizontal
R8, R19, R20, R21, R22, R23, R29, R33, R34, R35, R36, R37, R38, R39, R40, R49: 10k; R_Axial_DIN0207_L6.3mm_D2.5mm_P7.62mm_Horizontal
R42: 220R; R_Axial_DIN0207_L6.3mm_D2.5mm_P7.62mm_Horizontal
R44: 100R; R_Axial_DIN0411_L9.9mm_D3.6mm_P12.70mm_Horizontal
R51, R52, R53: 2R2; R_Axial_DIN0309_L9.0mm_D3.2mm_P12.70mm_Horizontal
U1: L7805; TO-220-3_Vertical

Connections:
12VRECT: C1.1, D2.1 (K), D3.1 (K), J5.1, R42.1, R44.2, U1.1 (IN)
+5V: C2.1, D3.2 (A), DB1.21 (5V5), R2.2, U1.3 (OUT)
+12V: D2.2 (A), J1.4, J2.4, J3.4, J4.4, R50.1
AUDIBLE: DB1.38 (41), R41.2
CONTINUITY1: D4.2 (A), R23.2, R37.1, R46.1
CONTINUITY2: D5.2 (A), R22.2, R38.1, R47.1
CONTINUITY3: D6.2 (A), R34.2, R39.1, R48.1
FAILSAFE: C3.1, C4.1, C5.1, J5.2, Q4.3 (C), Q8.3 (C), Q14.3 (C), R4.1, R7.1, R12.1, R13.1, R25.1, R26.1, R35.1
FAULT: DB1.41 (1), Q6.3 (C), Q12.3 (C), Q18.3 (C), R40.2
GND: C1.2, C2.2, C3.2, C4.2, C5.2, C6.2, C7.2, C8.2, C9.2, C10.2, C11.2, C12.2, C13.2, D1.1 (K), D4.1 (K), D5.1 (K), D6.1 (K), D7.1 (K), DB1.22 (GND), DB1.23 (GND), DB1.24 (GND), DB1.44 (GND), J4.1, J7.4, Q2.1 (E), Q3.3 (C), Q5.1 (E), Q6.1 (E), Q7.1 (E), Q9.3 (C), Q10.1 (E), Q12.1 (E), Q13.1 (E), Q15.3 (C), Q16.1 (E), Q18.1 (E), Q19.1 (E), Q20.1 (E), R1.2, R17.2, R20.2, R21.2, R29.2, R31.2, R45.2, R46.2, R47.2, R48.2, R49.2, R51.2, R52.2, R53.2, U1.2 (GND)
unnamed: C7.1, DB1.5, R37.2
unnamed: C8.1, DB1.6, R38.2
unnamed: C9.1, DB1.7, R39.2
unnamed: C14.2, R51.1
unnamed: C15.2, R52.1
unnamed: C16.2, R53.1
unnamed: D1.2 (A), R2.1
unnamed: D7.2 (A), R35.2, R36.2
unnamed: D8.2 (A), D9.1 (K)
unnamed: D8.1 (K), Q19.3 (C)
unnamed: D10.2 (A), R42.2
unnamed: D9.2 (A), D10.1 (K)
unnamed: D11.2 (A), J6.2, Q20.3 (C)
unnamed: D11.1 (K), J6.1, R44.1
unnamed: DB1.1 (3V3), R40.1
unnamed: C10.1, DB1.12 (8), R33.1
unnamed: C11.1, DB1.15 (9), R19.1
unnamed: C12.1, DB1.16 (10), R8.1
unnamed: DB1.18 (12), J7.1
unnamed: DB1.19 (13), J7.2
unnamed: DB1.20 (14), J7.3
unnamed: C14.1, J1.1, Q1.2 (D), R23.1
unnamed: C15.1, J2.1, Q11.2 (D), R22.1
unnamed: C16.1, J3.1, Q17.2 (D), R34.1
unnamed: Q1.1 (G), Q5.3 (C), R6.1, R20.1
unnamed: Q2.2 (B), R3.1, R7.2
unnamed: Q2.3 (C), R4.2, R5.2
unnamed: Q3.2 (B), Q4.2 (B), R5.1
unnamed: Q3.1 (E), Q4.1 (E), R6.2
unnamed: Q5.2 (B), R10.2
unnamed: Q6.2 (B), R9.1
unnamed: Q7.2 (B), R11.1, R12.2
unnamed: Q7.3 (C), R13.2, R14.2
unnamed: Q8.2 (B), Q9.2 (B), R14.1
unnamed: Q8.1 (E), Q9.1 (E), R15.2
unnamed: Q10.2 (B), R16.2
unnamed: Q10.3 (C), Q11.1 (G), R15.1, R21.1
unnamed: Q12.2 (B), R18.1
unnamed: Q13.2 (B), R24.1, R25.2
unnamed: Q13.3 (C), R26.2, R27.2
unnamed: Q14.2 (B), Q15.2 (B), R27.1
unnamed: Q14.1 (E), Q15.1 (E), R28.2
unnamed: Q16.2 (B), R30.2
unnamed: Q16.3 (C), Q17.1 (G), R28.1, R29.1
unnamed: Q18.2 (B), R32.1
unnamed: Q19.2 (B), R43.1
unnamed: Q20.2 (B), R41.1
PWRSENSE: C13.1, DB1.40 (2), R49.1, R50.2
SENSE1: Q1.3 (S), R1.1, R8.2, R9.2, R10.1
SENSE2: Q11.3 (S), R16.1, R17.1, R18.2, R19.2
SENSE3: Q17.3 (S), R30.1, R31.1, R32.2, R33.2
SENSEFAILSAFE: C6.1, DB1.4, R36.1, R45.1
TRIGGER1: DB1.11 (18), R3.2
TRIGGER2: DB1.10 (17), R11.2
TRIGGER3: DB1.9 (16), R24.2
VISIBLE: DB1.39 (42), R43.2

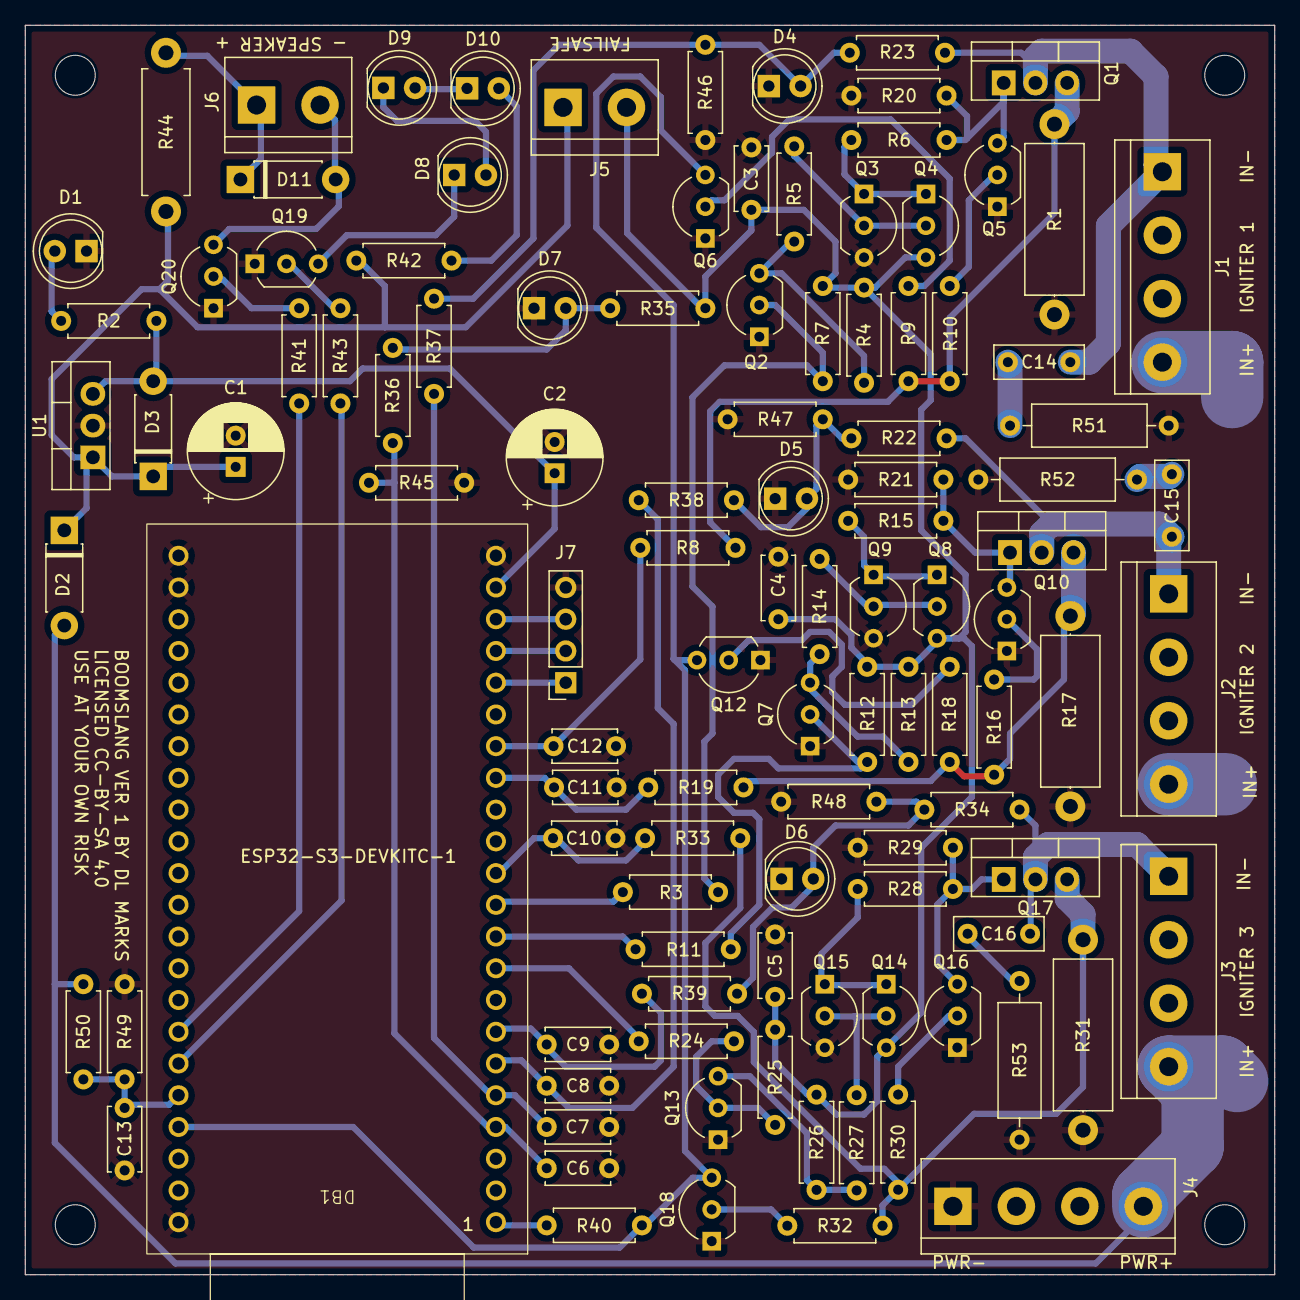
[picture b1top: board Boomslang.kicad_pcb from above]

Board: 2 copper layers, 100.0 x 100.0 mm, 113 parts (0 on the bottom side), 66 nets.

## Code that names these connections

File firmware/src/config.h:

#pragma once
#include <Arduino.h>

// Pin map, derived from Boomslang-schematic.pdf (DB1 = ESP32-S3-DevKitC-1).
//
// TRIGGER1/2/3 are ACTIVE LOW. Hardware pulls each trigger node toward the
// FAILSAFE arm rail through a 100k resistor, so a floating/undriven GPIO
// (reset, brownout, crash before setup() runs) reads as "not firing" as
// long as the physical arm key at J5 is open. Firmware must claim these
// pins and drive them HIGH before anything else, and must only ever pulse
// them LOW briefly to fire.
constexpr int NUM_CHANNELS = 3;
constexpr int PIN_TRIGGER[NUM_CHANNELS]    = { 18, 17, 16 };
constexpr int PIN_SENSE[NUM_CHANNELS]      = { 10, 9, 8 };  // firing-current shunt readback (0.05R)
constexpr int PIN_CONTINUITY[NUM_CHANNELS] = { 5, 6, 7 };   // igniter continuity readback (LED-clamped)

constexpr int PIN_SENSE_FAILSAFE = 4;  // arm-loop (J5) presence sense, same LED-clamp scheme
constexpr int PIN_FAULT          = 1;  // shared hardware overcurrent fault, active LOW, open-collector
constexpr int PIN_AUDIBLE        = 41; // buzzer driver (J6)
constexpr int PIN_VISIBLE        = 42; // onboard white/blue strobe LEDs
constexpr int PIN_BATTERY        = 2;  // 12V supply, through a 1:11 resistor divider

// LEDC channel/resolution for the arming buzzer (PIN_AUDIBLE). Driven
// directly via ledcWrite()/ledcChangeFrequency() rather than tone()/
// noTone() — ledcWriteTone() (which tone() calls internally) always
// forces exactly 50% duty on every call, which is incompatible with
// volume control (settings.speakerVolume): frequency and duty need to be
// set independently. 10-bit resolution matches what tone() itself used.
constexpr uint8_t AUDIBLE_LEDC_CHANNEL          = 0;
constexpr uint8_t AUDIBLE_LEDC_RESOLUTION_BITS  = 10;

// ADC scaling: 12-bit, 3.3V reference, 11dB attenuation.
constexpr float ADC_VREF   = 3.3f;
constexpr int   ADC_MAX    = 4095;

// CONTINUITY and SENSE_FAILSAFE both work by pushing ~1mA through a red LED
// and reading the clamped voltage across it: that LED's forward voltage
// exceeds this threshold when the sensed loop (igniter or arm switch) is
// actually closed, and the node floats near 0V when open. Same circuit,
// same threshold, for both.
constexpr float LED_CLAMP_ARM_VOLTS = 1.25f;
constexpr int CONTINUITY_OK_RAW = (int)(LED_CLAMP_ARM_VOLTS / ADC_VREF * ADC_MAX);
constexpr int FAILSAFE_OK_RAW   = CONTINUITY_OK_RAW;

// Firing current sense: SENSE node voltage = I_fire * senseOhms[ch], direct
// (no divider) since the ADC input draws negligible current. The per-channel
// shunt value itself is a runtime-configurable setting (see settings.h), not
// a compile-time constant — it's field-replaceable hardware.

// Battery/supply voltage sense: PIN_BATTERY sees the 12V rail through a
// fixed 1:11 resistor divider (a PCB-fixed ratio, not field-replaceable
// like the current-sense shunts, so this is a compile-time constant).
constexpr float BATTERY_DIVIDER_RATIO = 11.0f;

// The battery rail passes through a series diode before reaching the
// divider, so the sensed voltage reads low by that diode's forward drop
// regardless of divider ratio. Added back after scaling in
// readBatteryVoltage() to recover the true battery voltage.
constexpr float BATTERY_DIODE_DROP_V = 0.7f;

// Debug timing instrumentation: toggles PIN_DEBUG_TIMING high as the first
// thing onFaultISR() does and low once faultSampleTask finishes reading all
// three SENSE channels. Put a scope or logic analyzer on this pin alongside
// FAULT to measure real end-to-end latency on actual hardware. Set to 0 for
// a field build — it's harmless left on (one extra register write in the
// ISR, negligible), but there's no reason to carry it once timing is known.
#define DEBUG_FAULT_TIMING 1
// GPIO13 rather than an ADC1 pin like GPIO2 — this signal is purely
// digital, so it's worth leaving ADC-capable header pins free for actual
// analog sensing. GPIO13 is only on ADC2 (which conflicts with WiFi and so
// isn't a pin you'd want for real analog use anyway), and is otherwise
// unconnected on the PCB.
constexpr int PIN_DEBUG_TIMING = 13;

// Logs loop() iterations/sec (and average iteration time) over Serial
// once a second — added to measure the real achievable ceiling for
// channelPwmHz, since loop() can't toggle a PWM-cycled pin faster than it
// can complete one full pass (three analogRead() calls every iteration
// for the live current display dominate that time — see readCurrentA()
// callers). Set to 0 for a field build.
#define DEBUG_LOOP_RATE 1

// BENCH-DEBUG ONLY — normally onFaultISR() forces every TRIGGER pin high
// the instant FAULT asserts, and loop() calls stopSequence() on the
// transition into a latched fault, as a firmware-level echo of the
// per-channel hardware protection (Q5/Q10/Q16), which independently and
// unconditionally pulls a faulted channel's own MOSFET gate low in
// hardware regardless of this flag — that real transistor protection
// cannot be disabled from firmware at all. Setting this to 1 skips only
// firmware's redundant forced-HIGH/stopSequence() calls, so an in-progress
// pulse keeps running through a FAULT trip instead of being cut short —
// useful for diagnosing a suspected false trip (e.g. a switching
// transient) with no igniter/load connected. faultLatched is still set
// and still blocks new triggers until disarmed and genuinely resolved,
// same as always; only the forced shutoff of an already-running pulse is
// skipped. MUST be 0 for any real use with igniters/pyrotechnics connected.
#define DEBUG_DISABLE_FAULT_SHUTOFF 0

// Software leading-edge blanking: disables interrupts for a short,
// deterministic window around a *deliberate* trigger-pin write (start or
// end of a fire pulse), to filter the switching transient that was
// confirmed to be tripping FAULT with no load attached (the FAULT pin read
// high again immediately after, with DEBUG_DISABLE_FAULT_SHUTOFF on).
// Bench-validated at 10us: with 0 (no wait at all), FAULT's own comparator
// output hadn't necessarily finished settling by the time writeTrigger-
// PinBlanked() checks it, so a genuine fault could be missed by this
// function entirely (caught later, elsewhere, with no diagnostic snapshot)
// rather than filtered. 10us reliably avoids both that and the original
// no-load false trip. The delay also sets *where* on the fault current's
// natural rise/decay curve the diagnostic snapshot lands — shorter delay
// samples closer to the true peak (see readCurrentA() call sites), longer
// delay samples further into the decay; tune with a scope on
// PIN_DEBUG_TIMING/FAULT if the real transient/settling duration needs to
// be known precisely. 0 disables blanking (interrupts are still briefly
// disabled/re-enabled around the write, but with no added delay) — not
// recommended given the above.
constexpr uint32_t FAULT_BLANKING_US = 10;

// Factory-reset pin: pulled up internally, checked once at boot (see
// setup()). Ground it (jumper/button to GND) before power-up to reset all
// settings to their compiled-in defaults. GPIO14 has no strapping or other
// special function on the ESP32-S3, and is otherwise unconnected on the PCB.
constexpr int PIN_FACTORY_RESET = 14;

// How long setup() waits for a station-mode WiFi connection (settings.
// wifiStationMode) before giving up and falling back to hosting its own AP
// instead — see setup(). Trigger pins are already safely HIGH long before
// this runs, so blocking here just delays when the web UI comes up, not
// anything safety-relevant.
constexpr uint32_t WIFI_STA_CONNECT_TIMEOUT_MS = 15000;

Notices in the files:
Boomslang/Boomslang.kicad_pcb:
LICENSED CC-BY-SA 4.0
README.md:
Firmware License: MIT
Hardware License: CC BY-SA 4.0
